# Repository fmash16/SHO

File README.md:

# The SHO (ষ)

The ষ (SHO) is a 36 key choc spaced split keyboard based on the Seeduino XIAO controller. For the design, I took huge inspiration from the gergoplex which I love the look of. This keyboard uses the Seeduino Seed RP2040 as the MCU, which is really great for the price and the small size. Just love how compact it turned out coming from MX boards.

## Features:

1. XIAO RP 2040 / BLE controller for wired/wireless versions
2. Reversible PCBs
3. Soldered on Kailh Choc V1 switches (Choc whites in my build)
4. TRS/TRRS connection between both halves

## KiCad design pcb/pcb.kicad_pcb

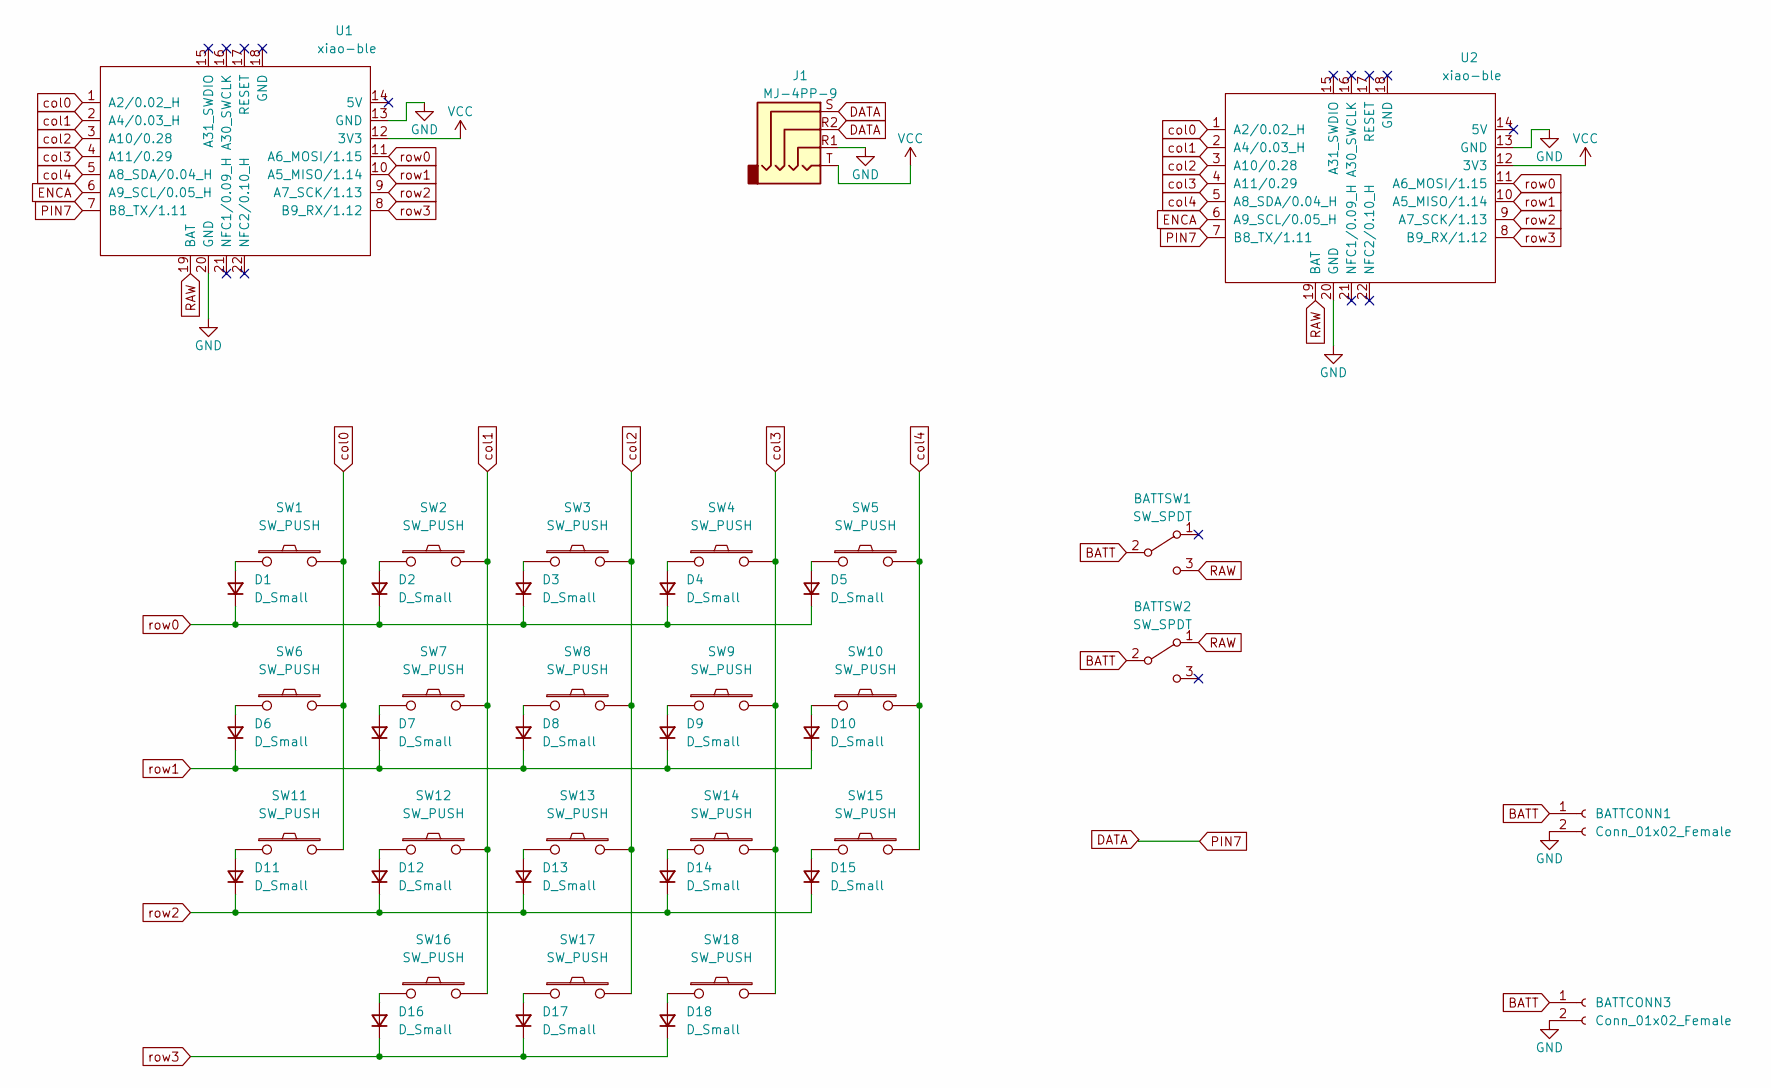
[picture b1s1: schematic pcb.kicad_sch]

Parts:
BATTCONN1, BATTCONN3: Conn_01x02_Female; Connector_JST-1x02-2.00mm
BATTSW1, BATTSW2: SW_SPDT; Switch_SPDT-PCM12
D1, D2, D3, D4, D5, D6, D7, D8, D9, D10, D11, D12, D13, D14, D15, D16, D17, D18: D_Small; Diode_1N4148-SOD123-reversible
J1: MJ-4PP-9; Connector_TRRS-reversible
SW1, SW2, SW3, SW4, SW5, SW6, SW7, SW8, SW9, SW10, SW11, SW12, SW13, SW14, SW15, SW16, SW17, SW18: SW_PUSH; Switch_ChocV1-reversible
U1, U2: xiao-ble; MCU_xiao-ble-smd

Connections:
BATT: BATTCONN1.1, BATTCONN3.1, BATTSW1.2 (B), BATTSW2.2 (B)
DATA: J1.R2, J1.S, U1.7 (B8_TX/1.11), U2.7 (B8_TX/1.11)
ENCA: U1.6 (A9_SCL/0.05_H), U2.6 (A9_SCL/0.05_H)
GND: BATTCONN1.2, BATTCONN3.2, J1.R1, U1.13 (GND), U1.20 (GND), U2.13 (GND), U2.20 (GND)
unnamed: D1.2 (A), SW1.1
unnamed: D2.2 (A), SW2.1
unnamed: D3.2 (A), SW3.1
unnamed: D4.2 (A), SW4.1
unnamed: D5.2 (A), SW5.1
unnamed: D6.2 (A), SW6.1
unnamed: D7.2 (A), SW7.1
unnamed: D8.2 (A), SW8.1
unnamed: D9.2 (A), SW9.1
unnamed: D10.2 (A), SW10.1
unnamed: D11.2 (A), SW11.1
unnamed: D12.2 (A), SW12.1
unnamed: D13.2 (A), SW13.1
unnamed: D14.2 (A), SW14.1
unnamed: D15.2 (A), SW15.1
unnamed: D16.2 (A), SW16.1
unnamed: D17.2 (A), SW17.1
unnamed: D18.2 (A), SW18.1
RAW: BATTSW1.3 (C), BATTSW2.1 (A), U1.19 (BAT), U2.19 (BAT)
VCC: J1.T, U1.12 (3V3), U2.12 (3V3)
col0: SW1.2, SW6.2, SW11.2, U1.1 (A2/0.02_H), U2.1 (A2/0.02_H)
col1: SW2.2, SW7.2, SW12.2, SW16.2, U1.2 (A4/0.03_H), U2.2 (A4/0.03_H)
col2: SW3.2, SW8.2, SW13.2, SW17.2, U1.3 (A10/0.28), U2.3 (A10/0.28)
col3: SW4.2, SW9.2, SW14.2, SW18.2, U1.4 (A11/0.29), U2.4 (A11/0.29)
col4: SW5.2, SW10.2, SW15.2, U1.5 (A8_SDA/0.04_H), U2.5 (A8_SDA/0.04_H)
row0: D1.1 (K), D2.1 (K), D3.1 (K), D4.1 (K), D5.1 (K), U1.11 (A6_MOSI/1.15), U2.11 (A6_MOSI/1.15)
row1: D6.1 (K), D7.1 (K), D8.1 (K), D9.1 (K), D10.1 (K), U1.10 (A5_MISO/1.14), U2.10 (A5_MISO/1.14)
row2: D11.1 (K), D12.1 (K), D13.1 (K), D14.1 (K), D15.1 (K), U1.9 (A7_SCK/1.13), U2.9 (A7_SCK/1.13)
row3: D16.1 (K), D17.1 (K), D18.1 (K), U1.8 (B9_RX/1.12), U2.8 (B9_RX/1.12)

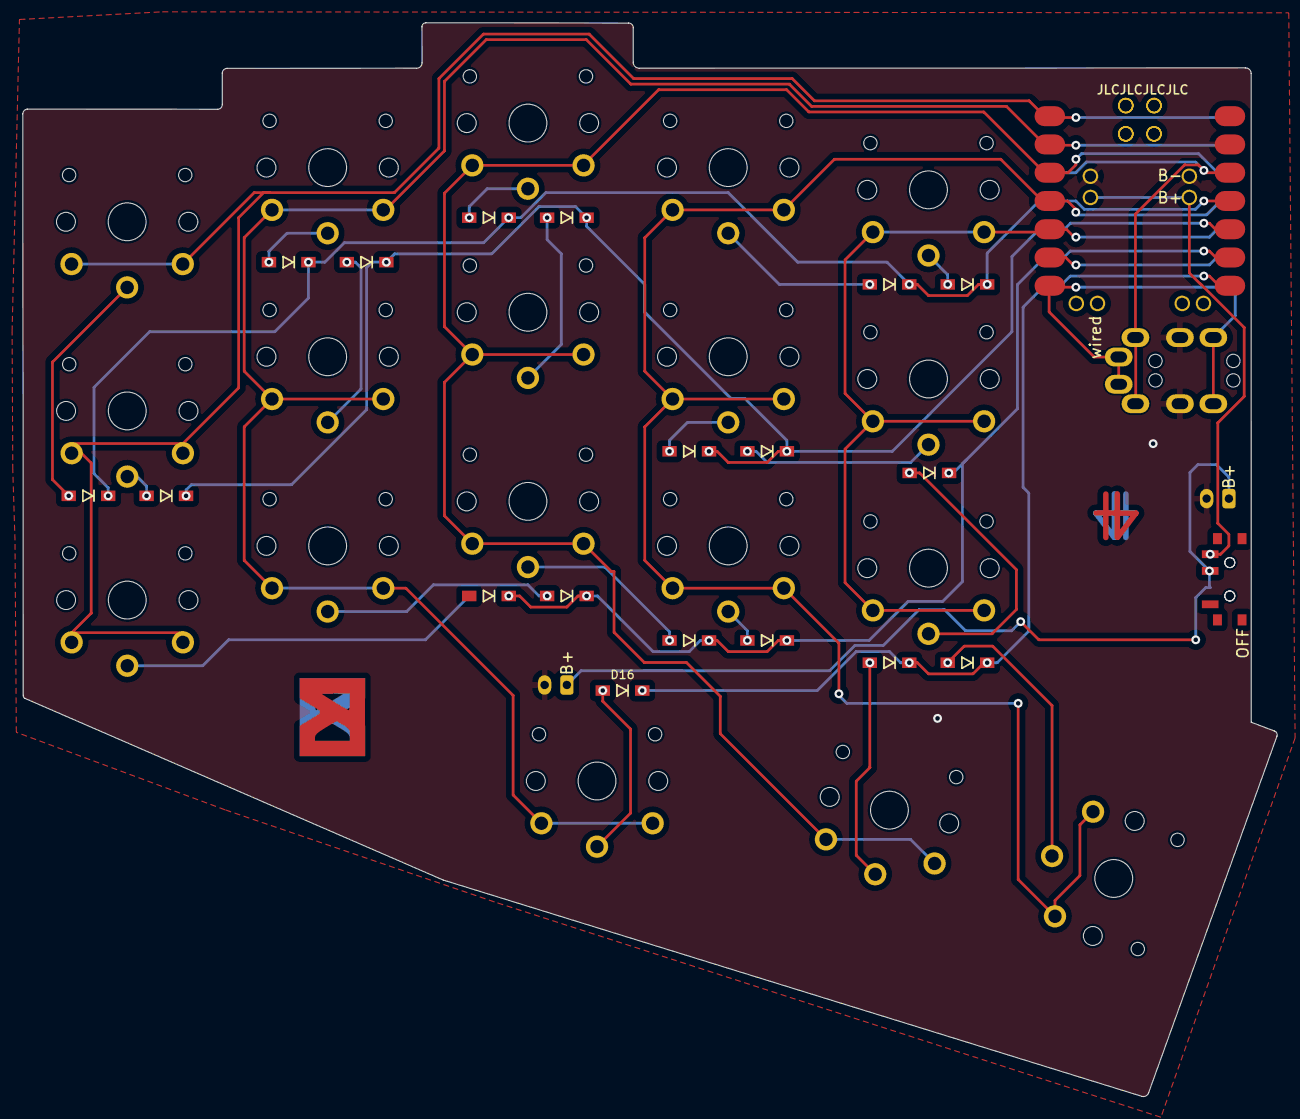
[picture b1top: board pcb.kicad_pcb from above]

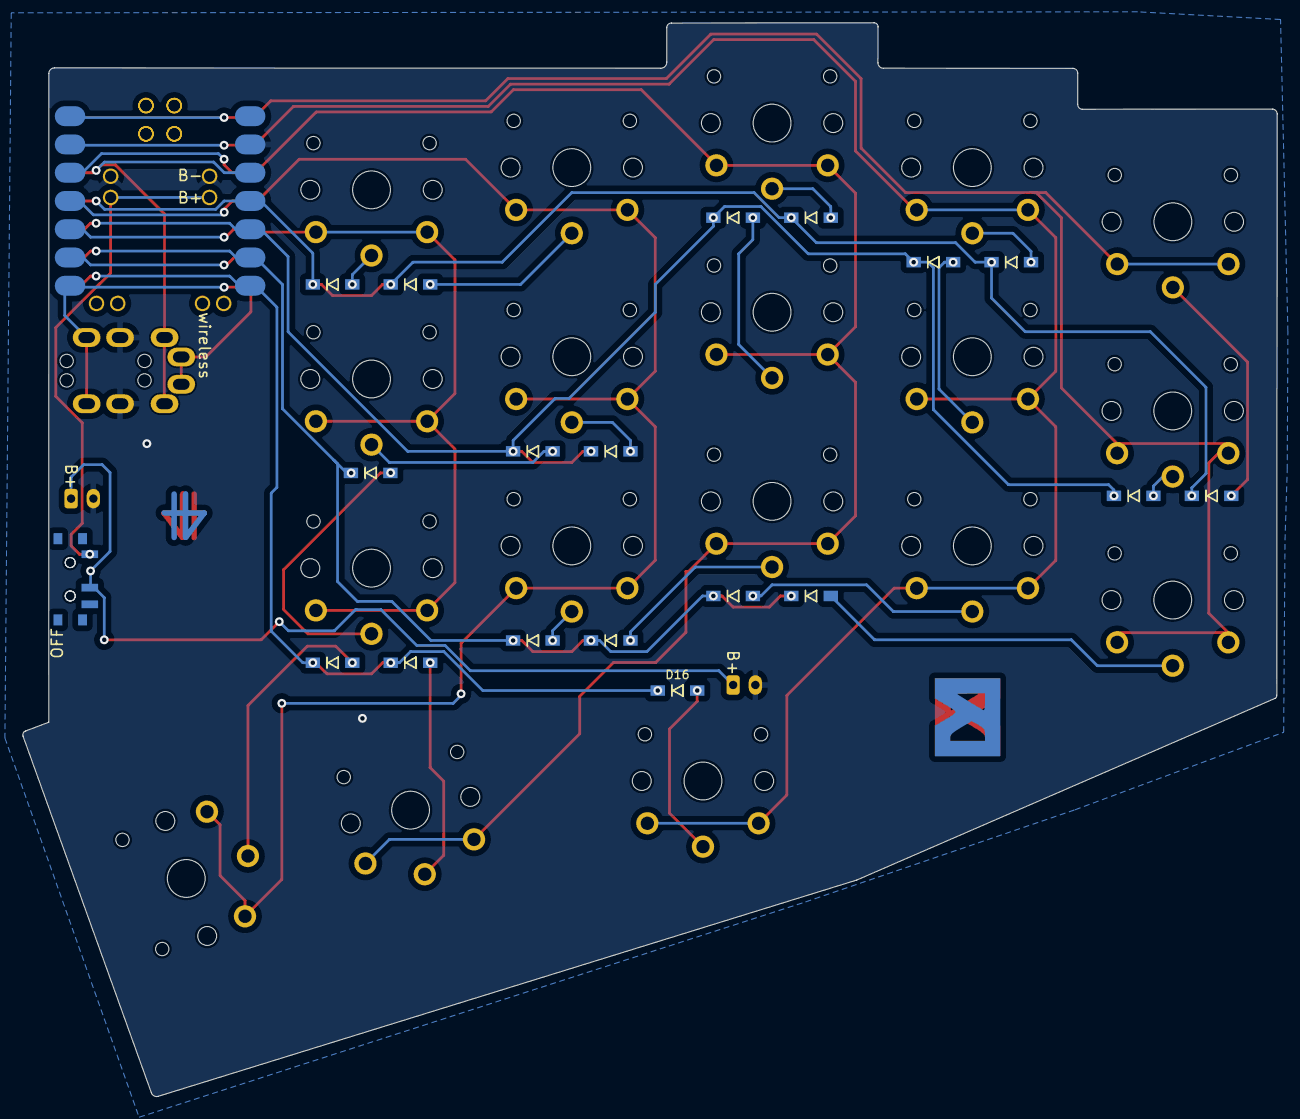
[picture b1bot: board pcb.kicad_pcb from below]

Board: 2 copper layers, 112.7 x 96.5 mm, 43 parts (2 on the bottom side), 33 nets.
